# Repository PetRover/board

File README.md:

# board
This repo is for keeping track of our board file

Final implementation video can be found on YouTube! 
https://youtu.be/edSjpHhAPHc

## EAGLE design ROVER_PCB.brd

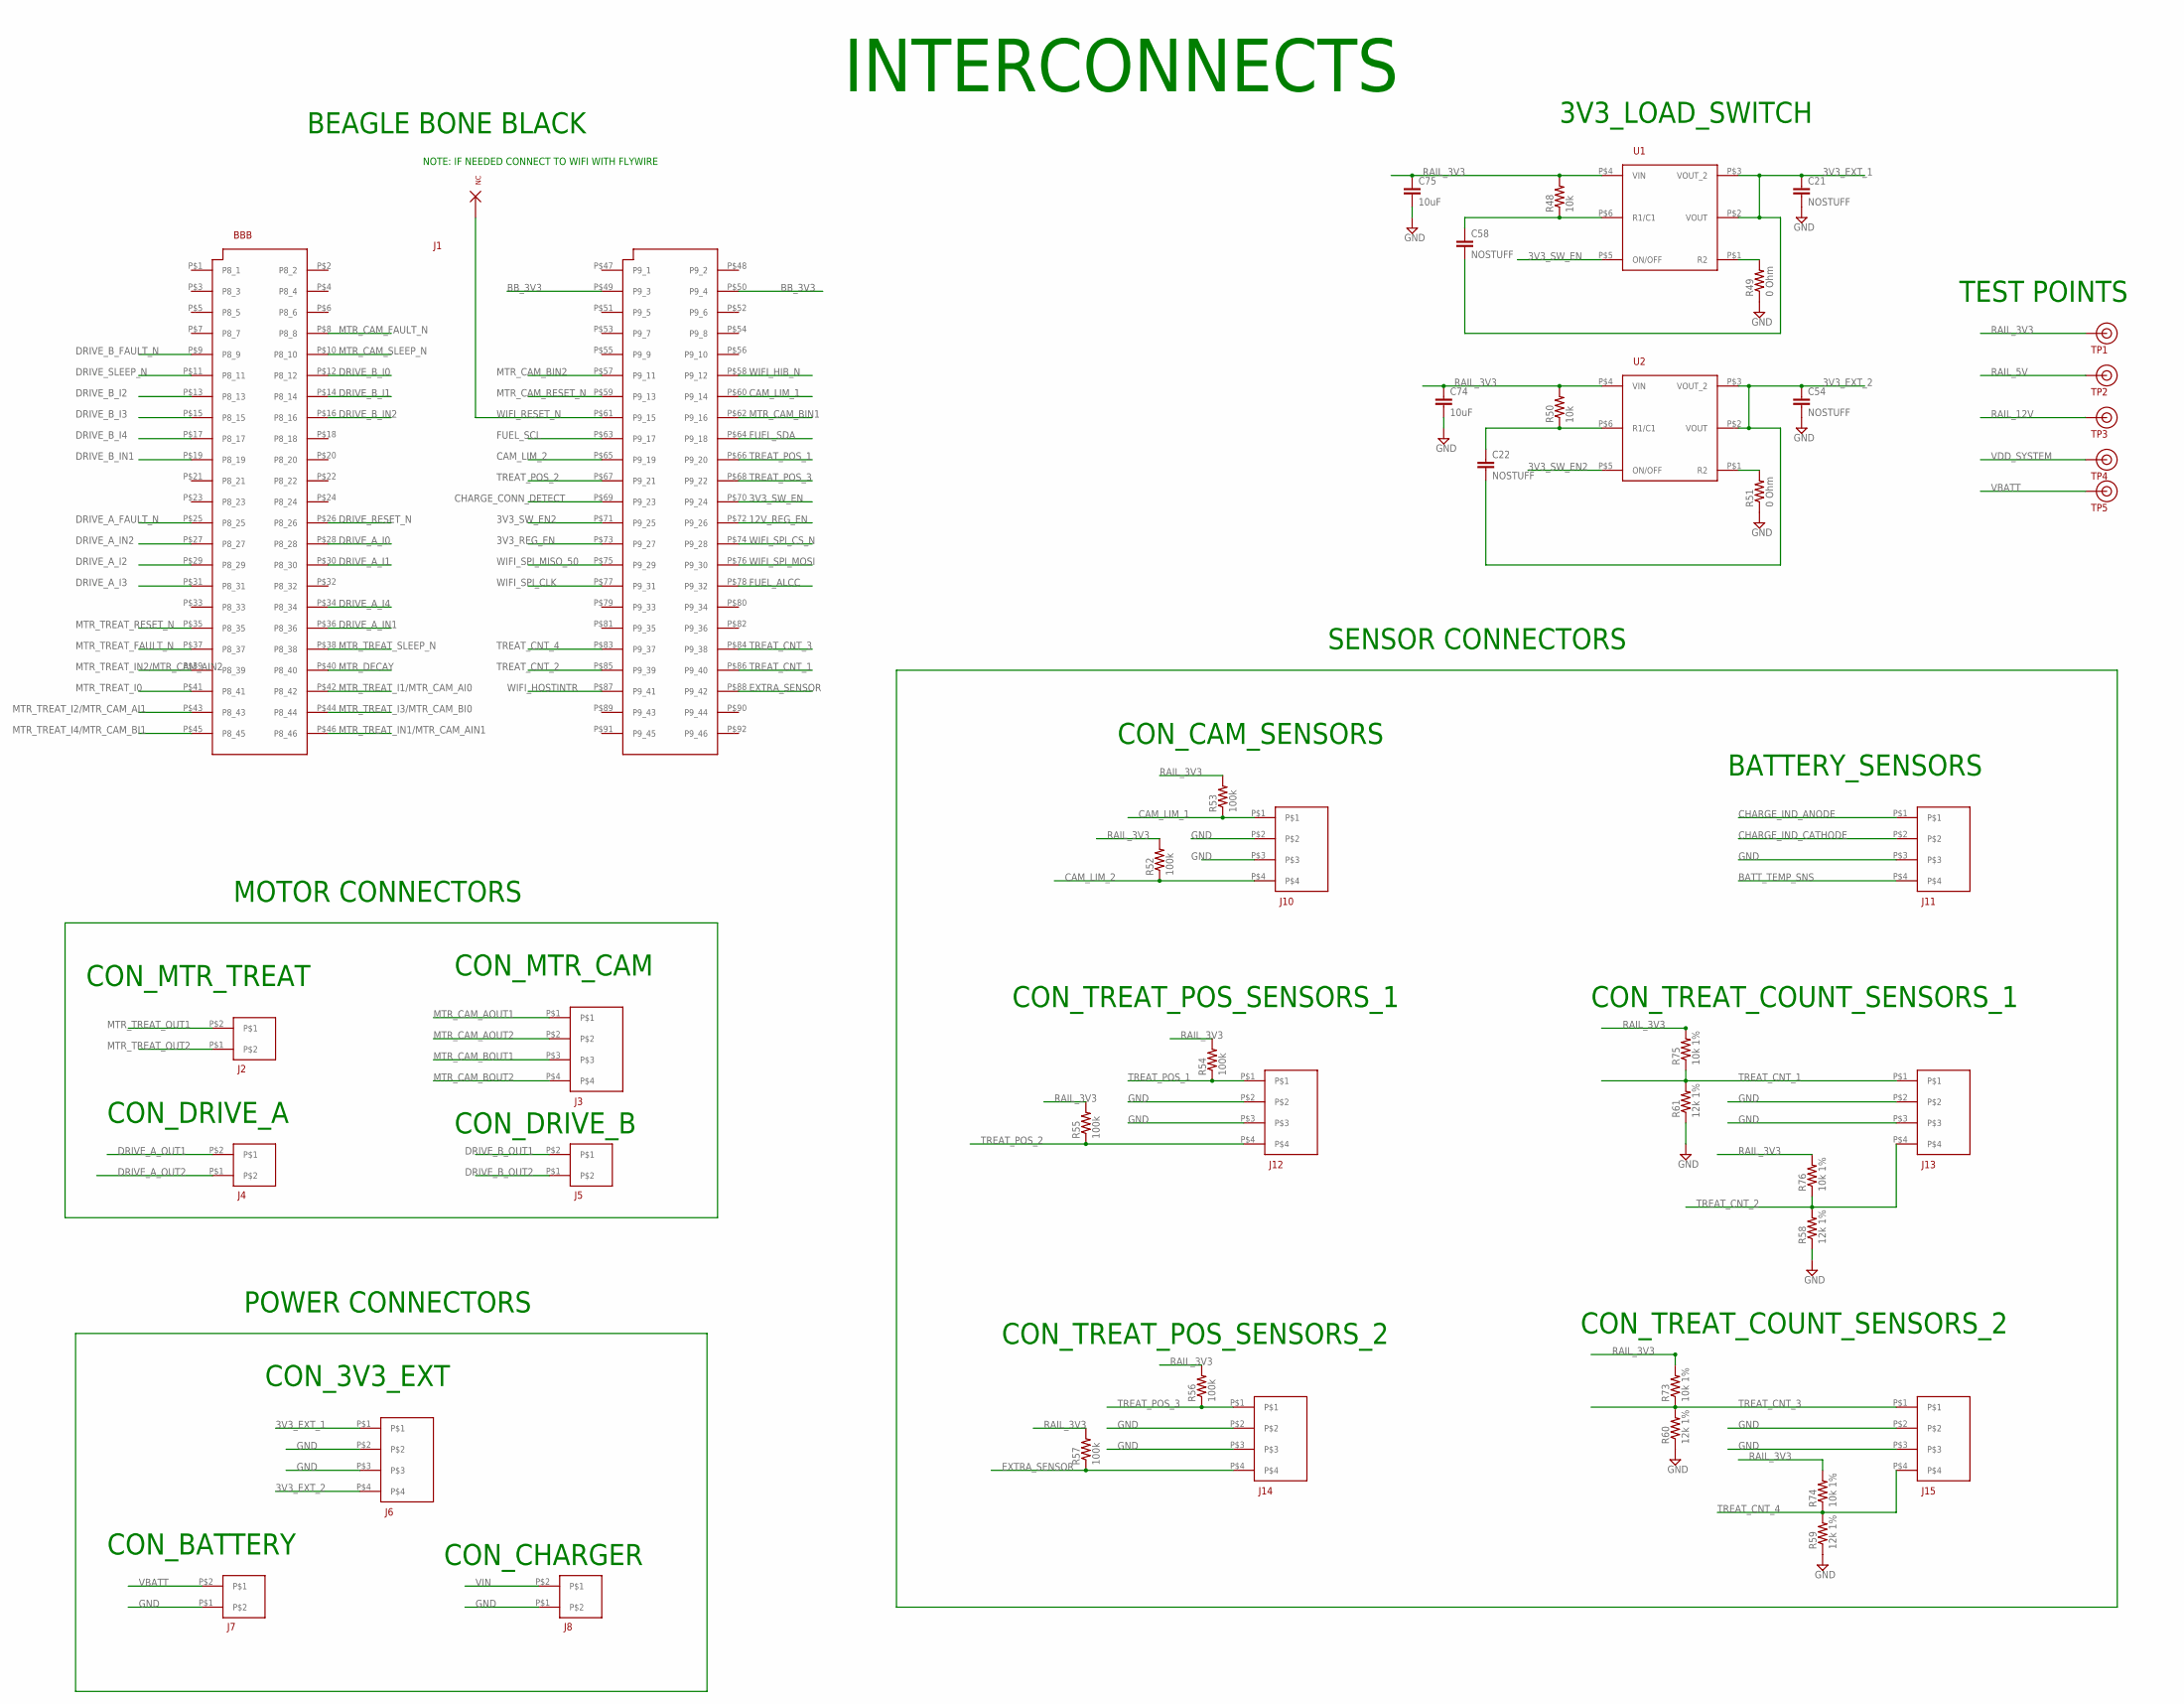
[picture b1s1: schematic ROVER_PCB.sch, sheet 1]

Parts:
C21, C22, C54, C58: NOSTUFF; C0402
C74, C75: 10uF; C0402
J1: NONE; BBB
J2, J4, J5, J7, J8: 2PIN_OST_3251
J3: 4PIN_OST_3251
J6, J10, J11, J12, J13, J14, J15: 4PIN_JST
R48, R50: 10k; R0603
R49, R51: 0 Ohm; R0603
R52, R53, R54, R55, R56, R57: 100k; R0603
R58, R59, R60, R61: 12k 1%; R0603
R73, R74, R75, R76: 10k 1%; R0603
TP1, TP2, TP3, TP4, TP5: TEST_POINT
U1, U2: TPS27081A

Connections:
3V3_EXT_1: C21.1, C58.2, J6.P$1, U1.P$2 (VOUT), U1.P$3 (VOUT_2)
3V3_EXT_2: C22.2, C54.1, J6.P$4, U2.P$2 (VOUT), U2.P$3 (VOUT_2)
3V3_REG_EN: J1.P$73 (P9_27); also elsewhere on the board
3V3_SW_EN: J1.P$70 (P9_24), U1.P$5 (ON/OFF)
3V3_SW_EN2: J1.P$71 (P9_25), U2.P$5 (ON/OFF)
12V_REG_EN: J1.P$72 (P9_26); also elsewhere on the board
BATT_TEMP_SNS: J11.P$4; also elsewhere on the board
BB_3V3: J1.P$49 (P9_3), J1.P$50 (P9_4); also elsewhere on the board
CAM_LIM_1: J1.P$60 (P9_14), J10.P$1, R53.1
CAM_LIM_2: J1.P$65 (P9_19), J10.P$4, R52.1
CHARGE_CONN_DETECT: J1.P$69 (P9_23); also elsewhere on the board
CHARGE_IND_ANODE: J11.P$1; also elsewhere on the board
CHARGE_IND_CATHODE: J11.P$2; also elsewhere on the board
DRIVE_A_FAULT_N: J1.P$25 (P8_25); also elsewhere on the board
DRIVE_A_I0: J1.P$28 (P8_28); also elsewhere on the board
DRIVE_A_I1: J1.P$30 (P8_30); also elsewhere on the board
DRIVE_A_I2: J1.P$29 (P8_29); also elsewhere on the board
DRIVE_A_I3: J1.P$31 (P8_31); also elsewhere on the board
DRIVE_A_I4: J1.P$34 (P8_34); also elsewhere on the board
DRIVE_A_IN1: J1.P$36 (P8_36); also elsewhere on the board
DRIVE_A_IN2: J1.P$27 (P8_27); also elsewhere on the board
DRIVE_A_OUT1: J4.P$2; also elsewhere on the board
DRIVE_A_OUT2: J4.P$1; also elsewhere on the board
DRIVE_B_FAULT_N: J1.P$9 (P8_9); also elsewhere on the board
DRIVE_B_I0: J1.P$12 (P8_12); also elsewhere on the board
DRIVE_B_I1: J1.P$14 (P8_14); also elsewhere on the board
DRIVE_B_I2: J1.P$13 (P8_13); also elsewhere on the board
DRIVE_B_I3: J1.P$15 (P8_15); also elsewhere on the board
DRIVE_B_I4: J1.P$17 (P8_17); also elsewhere on the board
DRIVE_B_IN1: J1.P$19 (P8_19); also elsewhere on the board
DRIVE_B_IN2: J1.P$16 (P8_16); also elsewhere on the board
DRIVE_B_OUT1: J5.P$2; also elsewhere on the board
DRIVE_B_OUT2: J5.P$1; also elsewhere on the board
DRIVE_RESET_N: J1.P$26 (P8_26); also elsewhere on the board
DRIVE_SLEEP_N: J1.P$11 (P8_11); also elsewhere on the board
EXTRA_SENSOR: J1.P$88 (P9_42), J14.P$4, R57.1
FUEL_ALCC: J1.P$78 (P9_32); also elsewhere on the board
FUEL_SCL: J1.P$63 (P9_17); also elsewhere on the board
FUEL_SDA: J1.P$64 (P9_18); also elsewhere on the board
GND: C21.2, C54.2, C74.2, C75.2, J6.P$2, J6.P$3, J7.P$1, J8.P$1, J10.P$2, J10.P$3, J11.P$3, J12.P$2, J12.P$3, J13.P$2, J13.P$3, J14.P$2, J14.P$3, J15.P$2, J15.P$3, R49.1, R51.1, R58.1, R59.1, R60.1, R61.1; also elsewhere on the board
MTR_CAM_AOUT1: J3.P$1; also elsewhere on the board
MTR_CAM_AOUT2: J3.P$2; also elsewhere on the board
MTR_CAM_BIN1: J1.P$62 (P9_16); also elsewhere on the board
MTR_CAM_BIN2: J1.P$57 (P9_11); also elsewhere on the board
MTR_CAM_BOUT1: J3.P$3; also elsewhere on the board
MTR_CAM_BOUT2: J3.P$4; also elsewhere on the board
MTR_CAM_FAULT_N: J1.P$8 (P8_8); also elsewhere on the board
MTR_CAM_RESET_N: J1.P$59 (P9_13); also elsewhere on the board
MTR_CAM_SLEEP_N: J1.P$10 (P8_10); also elsewhere on the board
MTR_DECAY: J1.P$40 (P8_40); also elsewhere on the board
MTR_TREAT_FAULT_N: J1.P$37 (P8_37); also elsewhere on the board
MTR_TREAT_I0: J1.P$41 (P8_41); also elsewhere on the board
MTR_TREAT_I1/MTR_CAM_AI0: J1.P$42 (P8_42); also elsewhere on the board
MTR_TREAT_I2/MTR_CAM_AI1: J1.P$43 (P8_43); also elsewhere on the board
MTR_TREAT_I3/MTR_CAM_BI0: J1.P$44 (P8_44); also elsewhere on the board
MTR_TREAT_I4/MTR_CAM_BI1: J1.P$45 (P8_45); also elsewhere on the board
MTR_TREAT_IN1/MTR_CAM_AIN1: J1.P$46 (P8_46); also elsewhere on the board
MTR_TREAT_IN2/MTR_CAM_AIN2: J1.P$39 (P8_39); also elsewhere on the board
MTR_TREAT_OUT1: J2.P$2; also elsewhere on the board
MTR_TREAT_OUT2: J2.P$1; also elsewhere on the board
MTR_TREAT_RESET_N: J1.P$35 (P8_35); also elsewhere on the board
MTR_TREAT_SLEEP_N: J1.P$38 (P8_38); also elsewhere on the board
unnamed: R49.2, U1.P$1 (R2)
unnamed: R51.2, U2.P$1 (R2)
unnamed: C58.1, R48.1, U1.P$6 (R1/C1)
unnamed: C22.1, R50.1, U2.P$6 (R1/C1)
RAIL_3V3: C74.1, C75.1, R48.2, R50.2, R52.2, R53.2, R54.2, R55.2, R56.2, R57.2, R73.2, R74.2, R75.2, R76.2, TP1.P$1, U1.P$4 (VIN), U2.P$4 (VIN); also elsewhere on the board
RAIL_5V: TP2.P$1; also elsewhere on the board
RAIL_12V: TP3.P$1; also elsewhere on the board
TREAT_CNT_1: J1.P$86 (P9_40), J13.P$1, R61.2, R75.1
TREAT_CNT_2: J1.P$85 (P9_39), J13.P$4, R58.2, R76.1
TREAT_CNT_3: J1.P$84 (P9_38), J15.P$1, R60.2, R73.1
TREAT_CNT_4: J1.P$83 (P9_37), J15.P$4, R59.2, R74.1
TREAT_POS_1: J1.P$66 (P9_20), J12.P$1, R54.1
TREAT_POS_2: J1.P$67 (P9_21), J12.P$4, R55.1
TREAT_POS_3: J1.P$68 (P9_22), J14.P$1, R56.1
VBATT: J7.P$2, TP5.P$1; also elsewhere on the board
VDD_SYSTEM: TP4.P$1; also elsewhere on the board
VIN: J8.P$2; also elsewhere on the board
WIFI_HIB_N: J1.P$58 (P9_12); also elsewhere on the board
WIFI_HOSTINTR: J1.P$87 (P9_41); also elsewhere on the board
WIFI_RESET_N: J1.P$61 (P9_15)
WIFI_SPI_CLK: J1.P$77 (P9_31); also elsewhere on the board
WIFI_SPI_CS_N: J1.P$74 (P9_28); also elsewhere on the board
WIFI_SPI_MISO_50: J1.P$75 (P9_29); also elsewhere on the board
WIFI_SPI_MOSI: J1.P$76 (P9_30); also elsewhere on the board

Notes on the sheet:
BEAGLE BONE BLACK
CON_BATTERY
CON_CHARGER
CON_DRIVE_A
CON_DRIVE_B
CON_MTR_TREAT
CON_MTR_CAM
CON_CAM_SENSORS
CON_TREAT_POS_SENSORS_1
CON_TREAT_POS_SENSORS_2
CON_TREAT_COUNT_SENSORS_2
CON_TREAT_COUNT_SENSORS_1
CON_3V3_EXT
3V3_LOAD_SWITCH
NOTE: IF NEEDED CONNECT TO WIFI WITH FLYWIRE
TEST POINTS
BATTERY_SENSORS
INTERCONNECTS
POWER CONNECTORS
MOTOR CONNECTORS
SENSOR CONNECTORS

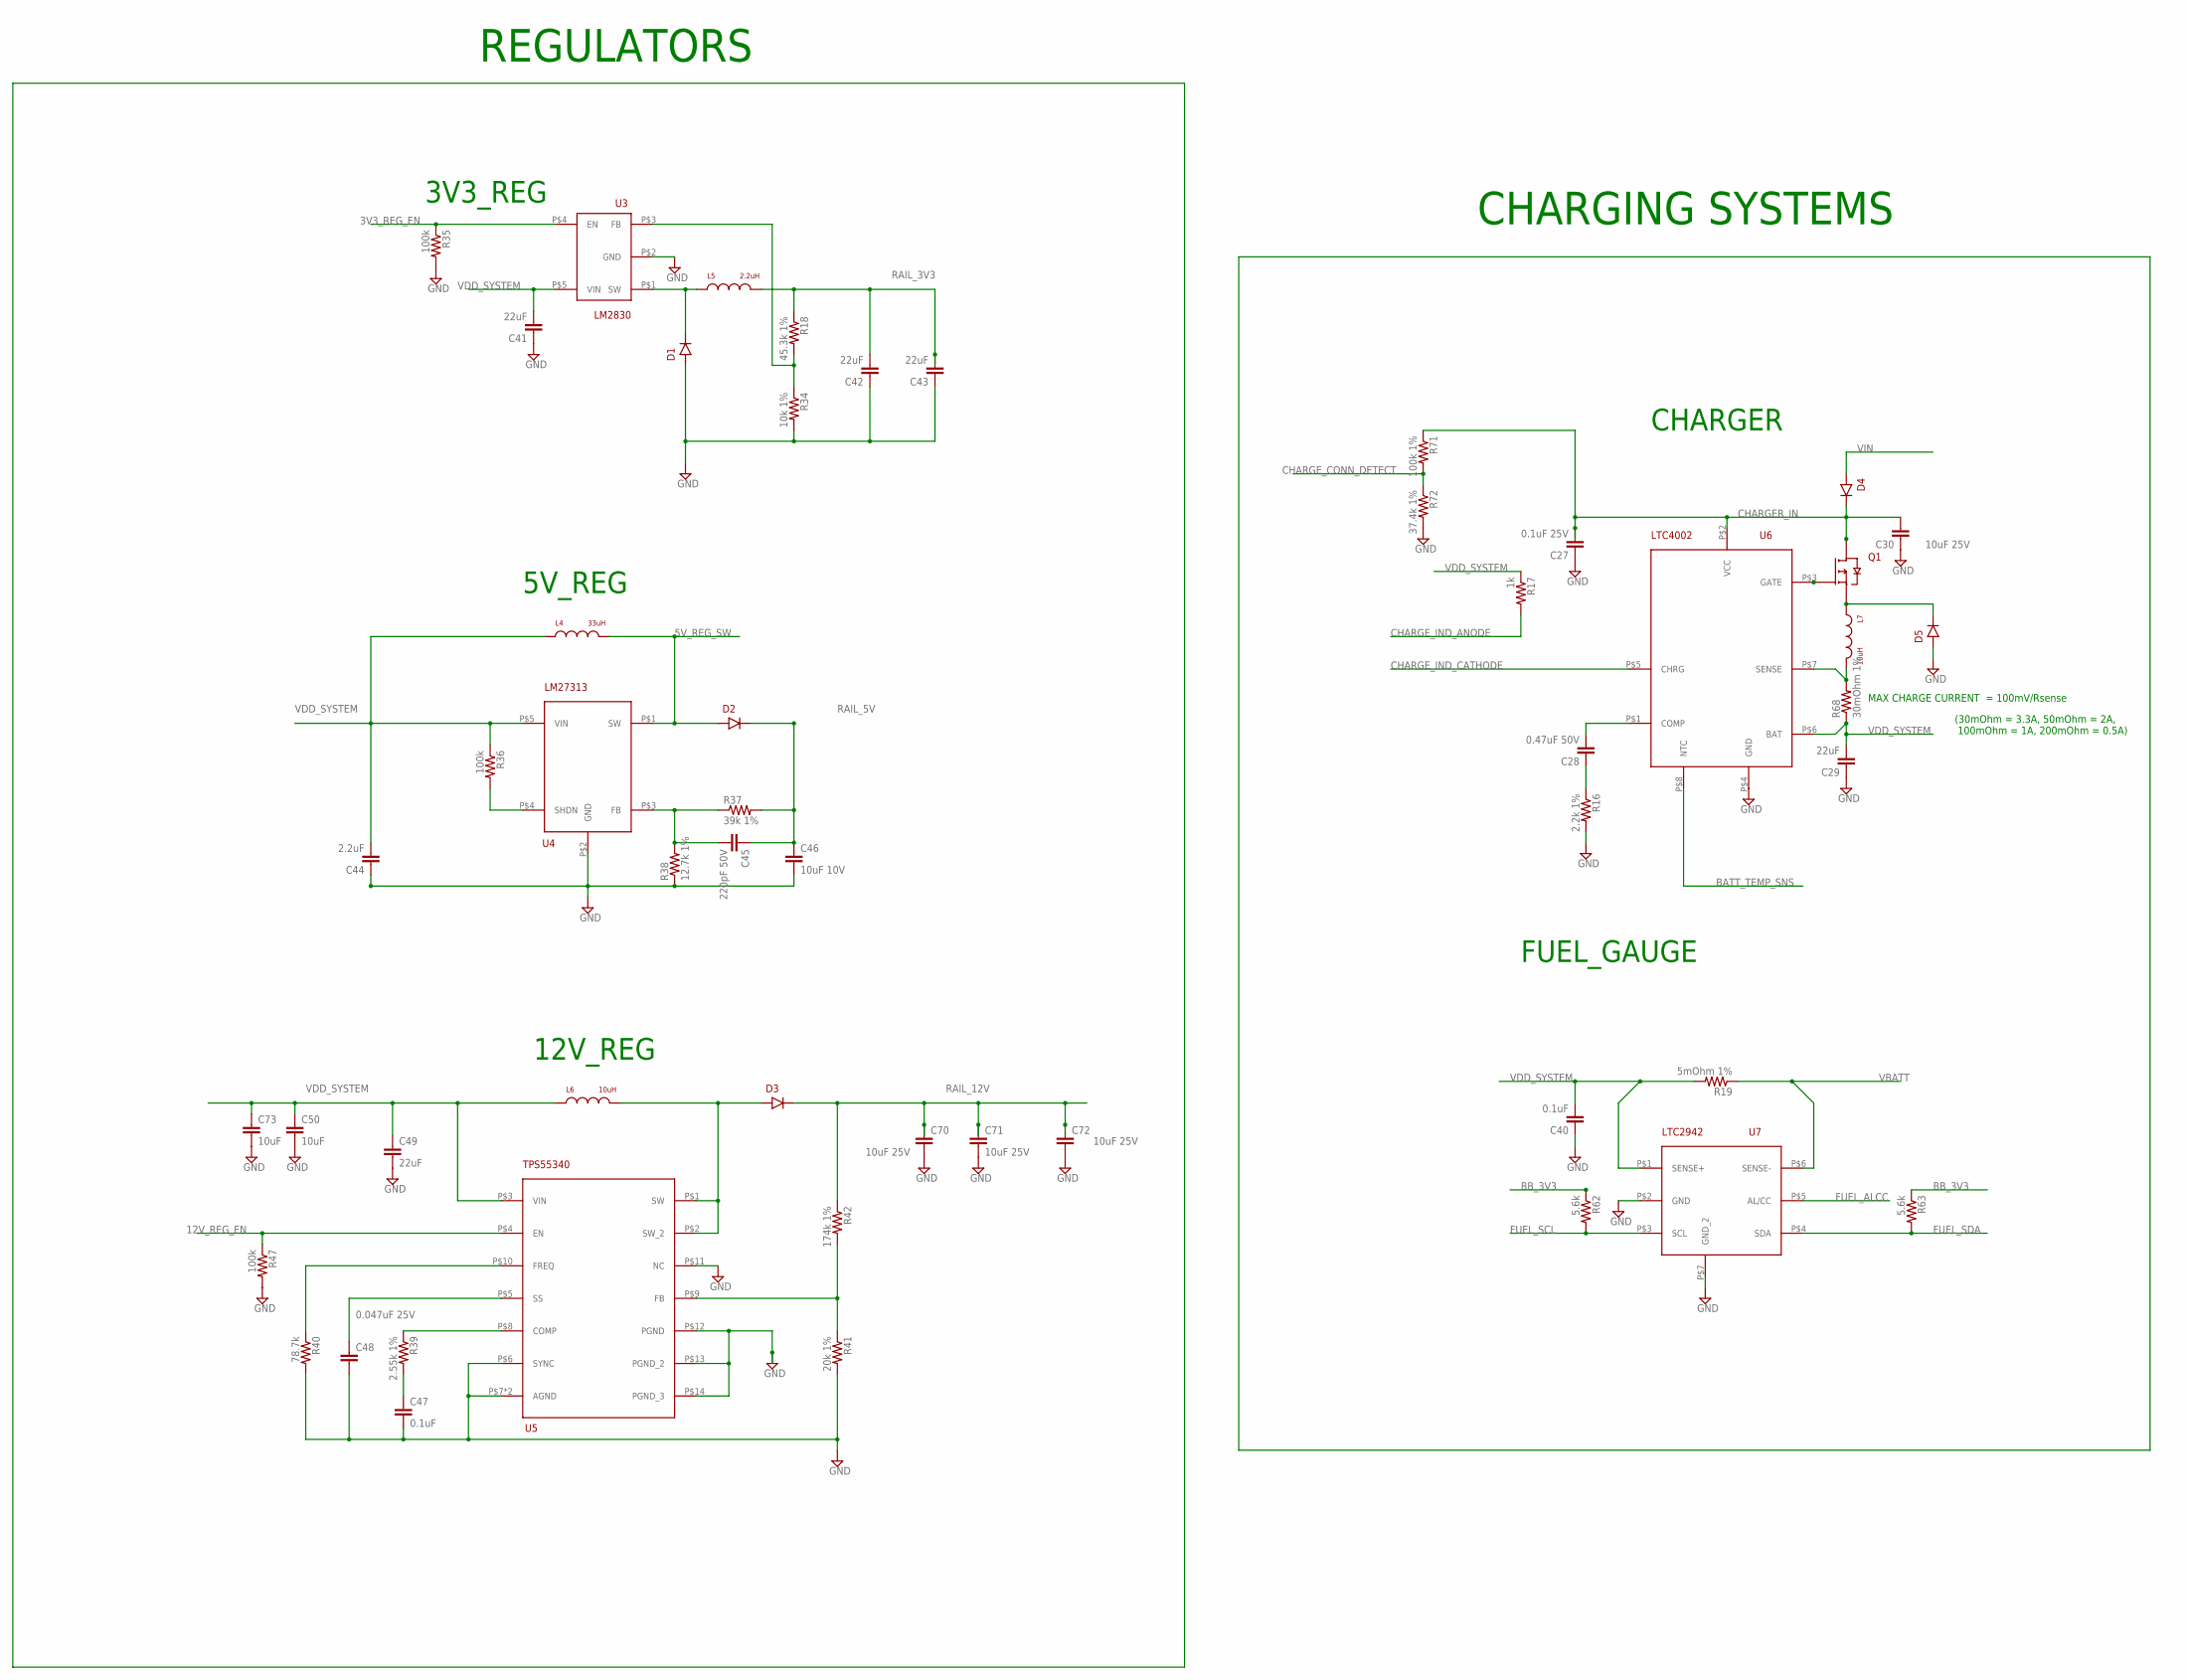
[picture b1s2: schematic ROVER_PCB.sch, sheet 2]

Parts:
C27: 0.1uF 25V; C0603
C28: 0.47uF 50V; C0603
C29, C41, C42, C43, C49: 22uF; C0603
C30, C70, C71, C72: 10uF 25V; C0603
C40, C47: 0.1uF; C0603
C44: 2.2uF; C0603
C45: 220pF 50V; C0603
C46: 10uF 10V; C0603
C48: 0.047uF 25V; C0603
C50, C73: 10uF; C0402
D1: CRS08
D2: MBR0520; MBR05XX
D3, D4, D5: B540C
L4: 33uH; AIUR-03
L5: 2.2uH; B82144B2222K
L6, L7: 10uH; ASPI-0630LR
Q1: AO3407A; SOT23
R16: 2.2k 1%; R0603
R17: 1k; R0603
R18: 45.3k 1%; R0603
R19: 5mOhm 1%; R2512
R34: 10k 1%; R0603
R35, R36, R47: 100k; R0603
R37: 39k 1%; R0603
R38: 12.7k 1%; R0603
R39: 2.55k 1%; R0603
R40: 78.7k; R0603
R41: 20k 1%; R0402
R42: 174k 1%; R0402
R62, R63: 5.6k; R0603
R68: 30mOhm 1%; R2512
R71: 100k 1%; R0603
R72: 37.4k 1%; R0603
U3: LM2830
U4: LM27313; LM2830
U5: TPS55340
U6: LTC4002
U7: LTC2942

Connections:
3V3_REG_EN: R35.1, U3.P$4 (EN); also elsewhere on the board
3V3_SW: D1.P$2, L5.P$1, U3.P$1 (SW)
5V_REG_SW: D2.P$1, L4.P$2, U4.P$1 (SW)
12V0_SW: D3.P$1, L6.P$2, U5.P$1 (SW), U5.P$2 (SW_2)
12V_REG_EN: R47.1, U5.P$4 (EN); also elsewhere on the board
BATT_TEMP_SNS: U6.P$8 (NTC); also elsewhere on the board
BB_3V3: R62.1, R63.1; also elsewhere on the board
CATCH_DIODE_CATHODE: D5.P$2, L7.P$1, Q1.2 (SOURE)
CHARGER_IN: C27.2, C30.2, D4.P$2, Q1.3 (DRAIN), R71.1, U6.P$2 (VCC)
CHARGE_CONN_DETECT: R71.2, R72.1; also elsewhere on the board
CHARGE_IND_ANODE: R17.2; also elsewhere on the board
CHARGE_IND_CATHODE: U6.P$5 (CHRG); also elsewhere on the board
CHARGE_SENSE_HI_SIDE: L7.P$2, R68.2, U6.P$7 (SENSE)
FUEL_ALCC: U7.P$5 (AL/CC); also elsewhere on the board
FUEL_SCL: R62.2, U7.P$3 (SCL); also elsewhere on the board
FUEL_SDA: R63.2, U7.P$4 (SDA); also elsewhere on the board
GND: C27.1, C29.1, C30.1, C40.1, C41.1, C42.1, C43.1, C44.1, C46.2, C47.2, C48.2, C49.2, C50.2, C70.2, C71.2, C72.2, C73.2, D1.P$1, D5.P$1, R16.2, R34.2, R35.2, R38.1, R40.2, R41.2, R47.2, R72.2, U3.P$2 (GND), U4.P$2 (GND), U5.P$6 (SYNC), U5.P$7 (AGND), U5.P$11 (NC), U5.P$12 (PGND), U5.P$13 (PGND_2), U5.P$14 (PGND_3), U5.P$15 (AGND), U6.P$4 (GND), U7.P$2 (GND), U7.P$7 (GND_2); also elsewhere on the board
unnamed: Q1.1 (GATE), U6.P$3 (GATE)
unnamed: C28.1, R16.1
unnamed: C28.2, U6.P$1 (COMP)
unnamed: R18.2, R34.1, U3.P$3 (FB)
unnamed: R39.1, U5.P$8 (COMP)
unnamed: C47.1, R39.2
unnamed: C48.1, U5.P$5 (SS)
unnamed: C45.2, R37.1, R38.2, U4.P$3 (FB)
unnamed: R40.1, U5.P$10 (FREQ)
unnamed: R41.1, R42.2, U5.P$9 (FB)
unnamed: R36.2, U4.P$4 (SHDN)
RAIL_3V3: C42.2, C43.2, L5.P$2, R18.1; also elsewhere on the board
RAIL_5V: C45.1, C46.1, D2.P$2, R37.2; also elsewhere on the board
RAIL_12V: C70.1, C71.1, C72.1, D3.P$2, R42.1; also elsewhere on the board
VBATT: R19.1, U7.P$6 (SENSE-); also elsewhere on the board
VDD_SYSTEM: C29.2, C40.2, C41.2, C44.2, C49.1, C50.1, C73.1, L4.P$1, L6.P$1, R17.1, R19.2, R36.1, R68.1, U3.P$5 (VIN), U4.P$5 (VIN), U5.P$3 (VIN), U6.P$6 (BAT), U7.P$1 (SENSE+); also elsewhere on the board
VIN: D4.P$1; also elsewhere on the board

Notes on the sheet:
3V3_REG
5V_REG
12V_REG
CHARGER
FUEL_GAUGE
MAX CHARGE CURRENT = 100mV/Rsense
REGULATORS
CHARGING SYSTEMS
(30mOhm = 3.3A, 50mOhm = 2A, 100mOhm = 1A, 200mOhm = 0.5A)

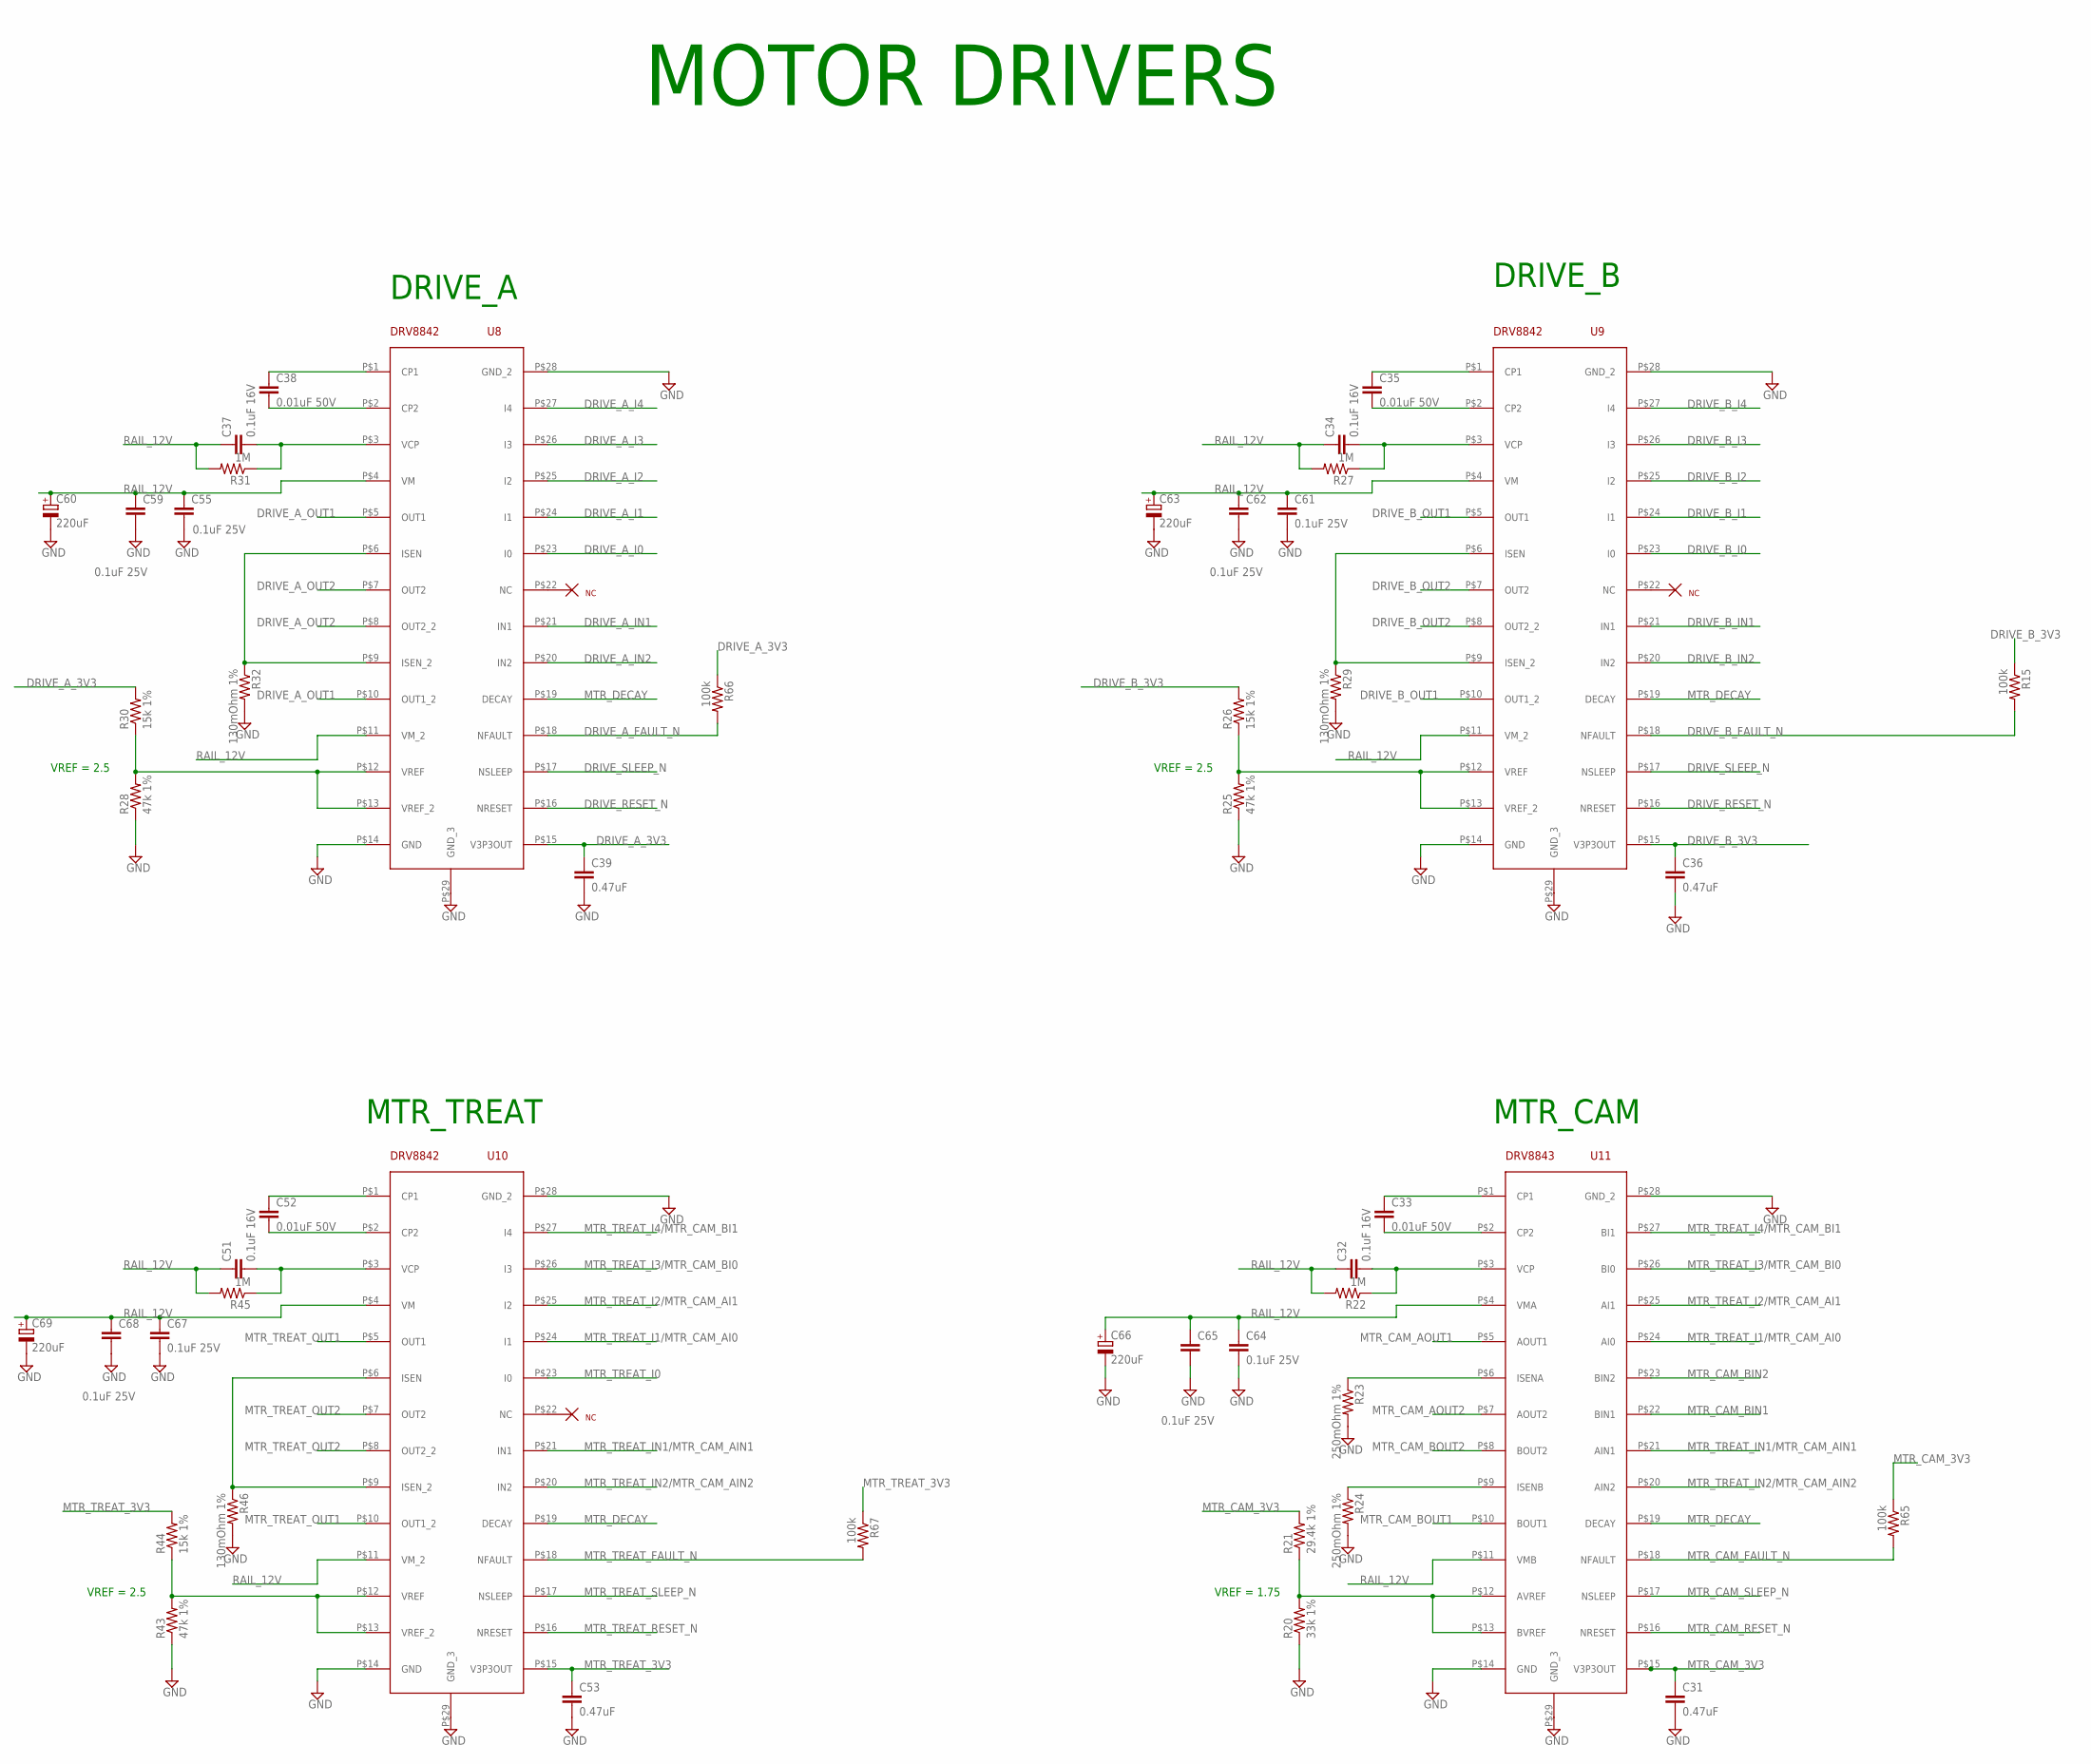
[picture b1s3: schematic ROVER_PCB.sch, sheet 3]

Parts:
C31, C36, C39, C53: 0.47uF; C0402
C32, C34, C37, C51: 0.1uF 16V; C0402
C33, C35, C38, C52: 0.01uF 50V; C0402
C55, C59, C61, C62, C64, C65, C67, C68: 0.1uF 25V; C0402
C60, C63, C66, C69: 220uF; E5-6
R15, R65, R66, R67: 100k; R0402
R20: 33k 1%; R0402
R21: 29.4k 1%; R0402
R22, R27, R31, R45: 1M; R0402
R23, R24: 250mOhm 1%; R1206
R25, R28, R43: 47k 1%; R0402
R26, R30, R44: 15k 1%; R0402
R29, R32, R46: 130mOhm 1%; R2512
U8, U9, U10: DRV8842
U11: DRV8843; DRV8842

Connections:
DRIVE_A_3V3: C39.1, R30.2, R66.1, U8.P$15 (V3P3OUT)
DRIVE_A_FAULT_N: R66.2, U8.P$18 (NFAULT); also elsewhere on the board
DRIVE_A_I0: U8.P$23 (I0); also elsewhere on the board
DRIVE_A_I1: U8.P$24 (I1); also elsewhere on the board
DRIVE_A_I2: U8.P$25 (I2); also elsewhere on the board
DRIVE_A_I3: U8.P$26 (I3); also elsewhere on the board
DRIVE_A_I4: U8.P$27 (I4); also elsewhere on the board
DRIVE_A_IN1: U8.P$21 (IN1); also elsewhere on the board
DRIVE_A_IN2: U8.P$20 (IN2); also elsewhere on the board
DRIVE_A_OUT1: U8.P$5 (OUT1), U8.P$10 (OUT1_2); also elsewhere on the board
DRIVE_A_OUT2: U8.P$7 (OUT2), U8.P$8 (OUT2_2); also elsewhere on the board
DRIVE_B_3V3: C36.1, R15.1, R26.2, U9.P$15 (V3P3OUT)
DRIVE_B_FAULT_N: R15.2, U9.P$18 (NFAULT); also elsewhere on the board
DRIVE_B_I0: U9.P$23 (I0); also elsewhere on the board
DRIVE_B_I1: U9.P$24 (I1); also elsewhere on the board
DRIVE_B_I2: U9.P$25 (I2); also elsewhere on the board
DRIVE_B_I3: U9.P$26 (I3); also elsewhere on the board
DRIVE_B_I4: U9.P$27 (I4); also elsewhere on the board
DRIVE_B_IN1: U9.P$21 (IN1); also elsewhere on the board
DRIVE_B_IN2: U9.P$20 (IN2); also elsewhere on the board
DRIVE_B_OUT1: U9.P$5 (OUT1), U9.P$10 (OUT1_2); also elsewhere on the board
DRIVE_B_OUT2: U9.P$7 (OUT2), U9.P$8 (OUT2_2); also elsewhere on the board
DRIVE_RESET_N: U8.P$16 (NRESET), U9.P$16 (NRESET); also elsewhere on the board
DRIVE_SLEEP_N: U8.P$17 (NSLEEP), U9.P$17 (NSLEEP); also elsewhere on the board
GND: C31.2, C36.2, C39.2, C53.2, C55.2, C59.2, C60.-, C61.2, C62.2, C63.-, C64.2, C65.2, C66.-, C67.2, C68.2, C69.-, R20.1, R23.2, R24.2, R25.1, R28.1, R29.2, R32.2, R43.1, R46.2, U8.P$14 (GND), U8.P$28 (GND_2), U8.P$29 (GND_3), U9.P$14 (GND), U9.P$28 (GND_2), U9.P$29 (GND_3), U10.P$14 (GND), U10.P$28 (GND_2), U10.P$29 (GND_3), U11.P$14 (GND), U11.P$28 (GND_2), U11.P$29 (GND_3); also elsewhere on the board
MTR_CAM_3V3: C31.1, R21.2, R65.1, U11.P$15 (V3P3OUT)
MTR_CAM_AOUT1: U11.P$5 (AOUT1); also elsewhere on the board
MTR_CAM_AOUT2: U11.P$7 (AOUT2); also elsewhere on the board
MTR_CAM_BIN1: U11.P$22 (BIN1); also elsewhere on the board
MTR_CAM_BIN2: U11.P$23 (BIN2); also elsewhere on the board
MTR_CAM_BOUT1: U11.P$10 (BOUT1); also elsewhere on the board
MTR_CAM_BOUT2: U11.P$8 (BOUT2); also elsewhere on the board
MTR_CAM_FAULT_N: R65.2, U11.P$18 (NFAULT); also elsewhere on the board
MTR_CAM_RESET_N: U11.P$16 (NRESET); also elsewhere on the board
MTR_CAM_SLEEP_N: U11.P$17 (NSLEEP); also elsewhere on the board
MTR_DECAY: U8.P$19 (DECAY), U9.P$19 (DECAY), U10.P$19 (DECAY), U11.P$19 (DECAY); also elsewhere on the board
MTR_TREAT_3V3: C53.1, R44.2, R67.1, U10.P$15 (V3P3OUT)
MTR_TREAT_FAULT_N: R67.2, U10.P$18 (NFAULT); also elsewhere on the board
MTR_TREAT_I0: U10.P$23 (I0); also elsewhere on the board
MTR_TREAT_I1/MTR_CAM_AI0: U10.P$24 (I1), U11.P$24 (AI0); also elsewhere on the board
MTR_TREAT_I2/MTR_CAM_AI1: U10.P$25 (I2), U11.P$25 (AI1); also elsewhere on the board
MTR_TREAT_I3/MTR_CAM_BI0: U10.P$26 (I3), U11.P$26 (BI0); also elsewhere on the board
MTR_TREAT_I4/MTR_CAM_BI1: U10.P$27 (I4), U11.P$27 (BI1); also elsewhere on the board
MTR_TREAT_IN1/MTR_CAM_AIN1: U10.P$21 (IN1), U11.P$21 (AIN1); also elsewhere on the board
MTR_TREAT_IN2/MTR_CAM_AIN2: U10.P$20 (IN2), U11.P$20 (AIN2); also elsewhere on the board
MTR_TREAT_OUT1: U10.P$5 (OUT1), U10.P$10 (OUT1_2); also elsewhere on the board
MTR_TREAT_OUT2: U10.P$7 (OUT2), U10.P$8 (OUT2_2); also elsewhere on the board
MTR_TREAT_RESET_N: U10.P$16 (NRESET); also elsewhere on the board
MTR_TREAT_SLEEP_N: U10.P$17 (NSLEEP); also elsewhere on the board
unnamed: R43.2, R44.1, U10.P$12 (VREF), U10.P$13 (VREF_2)
unnamed: C52.1, U10.P$1 (CP1)
unnamed: C52.2, U10.P$2 (CP2)
unnamed: R46.1, U10.P$6 (ISEN), U10.P$9 (ISEN_2)
unnamed: C51.2, R45.1, U10.P$3 (VCP)
unnamed: R20.2, R21.1, U11.P$12 (AVREF), U11.P$13 (BVREF)
unnamed: C33.1, U11.P$1 (CP1)
unnamed: C33.2, U11.P$2 (CP2)
unnamed: R23.1, U11.P$6 (ISENA)
unnamed: R24.1, U11.P$9 (ISENB)
unnamed: C32.2, R22.1, U11.P$3 (VCP)
unnamed: R28.2, R30.1, U8.P$12 (VREF), U8.P$13 (VREF_2)
unnamed: R25.2, R26.1, U9.P$12 (VREF), U9.P$13 (VREF_2)
unnamed: C35.1, U9.P$1 (CP1)
unnamed: C35.2, U9.P$2 (CP2)
unnamed: R29.1, U9.P$6 (ISEN), U9.P$9 (ISEN_2)
unnamed: C38.1, U8.P$1 (CP1)
unnamed: C34.2, R27.1, U9.P$3 (VCP)
unnamed: C38.2, U8.P$2 (CP2)
unnamed: R32.1, U8.P$6 (ISEN), U8.P$9 (ISEN_2)
unnamed: C37.2, R31.1, U8.P$3 (VCP)
RAIL_12V: C32.1, C34.1, C37.1, C51.1, C55.1, C59.1, C60.+, C61.1, C62.1, C63.+, C64.1, C65.1, C66.+, C67.1, C68.1, C69.+, R22.2, R27.2, R31.2, R45.2, U8.P$4 (VM), U8.P$11 (VM_2), U9.P$4 (VM), U9.P$11 (VM_2), U10.P$4 (VM), U10.P$11 (VM_2), U11.P$4 (VMA), U11.P$11 (VMB); also elsewhere on the board

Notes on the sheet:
DRIVE_A
DRIVE_B
MTR_TREAT
MTR_CAM
MOTOR DRIVERS
VREF = 1.75
VREF = 2.5
